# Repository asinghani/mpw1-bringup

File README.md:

# mpw1-bringup

Experiments in salvating SKY130 MPW-ONE chips, 1.5 years after the initial tapeout in December 2020.

### Background

MPW-ONE was the first round of the open-source Google-sponsored tapeout, and as a result of tooling issues with the clock-tree verification, the standard "caravel" padframe used for all chips on the MPW contains timing violations. In this repo I am working with my submission to MPW-ONE and attempting to recover functionality using precise voltage and clock control to reduce the significance of these issues - [asinghani/crypto-accelerator-chip](https://github.com/asinghani/crypto-accelerator-chip)

### Board images

### Progress

- Designed test board (see images above) with a Raspberry Pi Pico and DAC8571
- Implemented firmware (`ctrlfw/remote_ctrl_fw`) and associated Jupyter Notebooks (`notebooks/characterization.ipynb`) for searching possible voltages
- Tested ~50 dies and found some that produced sufficient activity on the Flash memory bus
- Implemented communication protocol in RISC-V assembly which allows bytes to be bit-banged (independent of clock frequency) through the single Caravel GPIO port. This means that non-default GPIO does not need to be enabled in order to get data out of the Caravel core.
- Used this protocol to read the identifier ROMs in the SHA256 and AES cores
- Wrote RISC-V code to Caravel to run short tests of SHA256 and AES256 operations

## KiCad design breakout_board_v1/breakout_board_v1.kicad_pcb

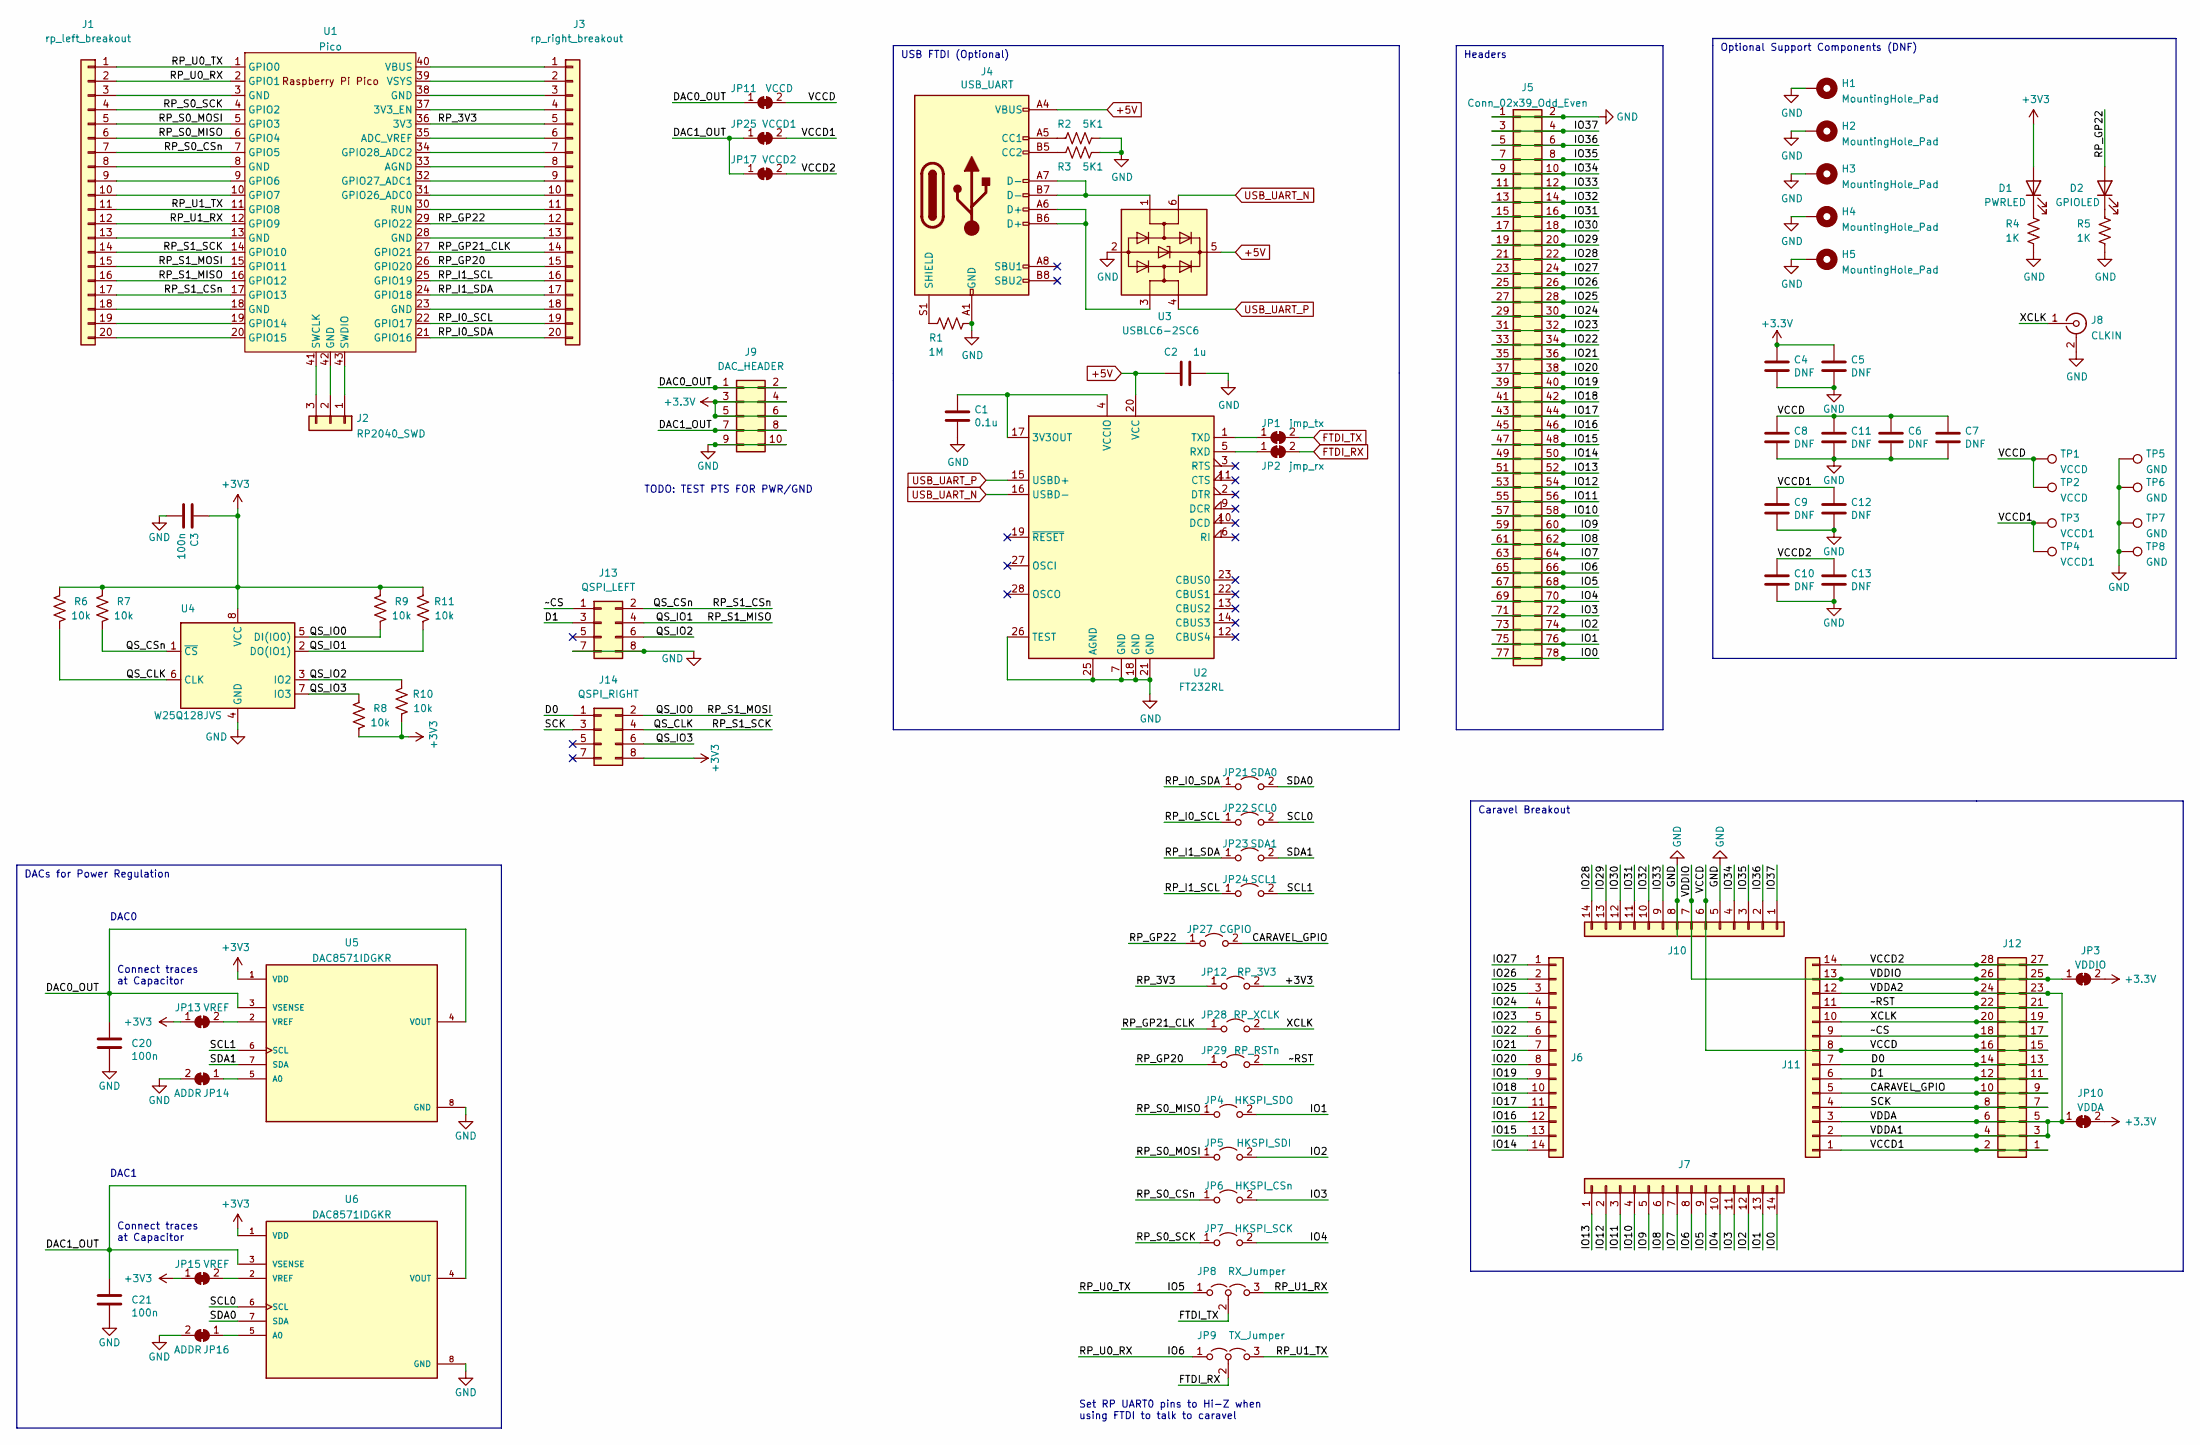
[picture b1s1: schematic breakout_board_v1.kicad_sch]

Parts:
C1: 0.1u; C_0603_1608Metric
C2: 1u; C_0603_1608Metric
C3, C20, C21: 100n; C_0603_1608Metric
C4, C5, C6, C7, C8, C9, C10, C11, C12, C13: DNF; C_0603_1608Metric
D1: PWRLED; LED_0805_2012Metric
D2: GPIOLED; LED_0805_2012Metric
H1, H2, H3, H4, H5: MountingHole_Pad; MountingHole_3.2mm_M3_Pad_Via
J1: rp_left_breakout; PinHeader_1x20_P2.54mm_Vertical
J2: RP2040_SWD; PinHeader_1x03_P2.54mm_Vertical
J3: rp_right_breakout; PinHeader_1x20_P2.54mm_Vertical
J4: USB_UART; USB_C_Receptacle_HRO_TYPE-C-31-M-12
J5: Conn_02x39_Odd_Even; PinHeader_2x39_P2.54mm_Vertical
J6, J7, J10, J11: Conn_01x14; PinHeader_1x14_P1.27mm_Vertical
J8: CLKIN; SMA_Amphenol_132289_EdgeMount
J9: DAC_HEADER; PinHeader_2x05_P2.54mm_Vertical
J12: Conn_02x14_Odd_Even; PinHeader_2x14_P2.54mm_Vertical
J13: QSPI_LEFT; PinHeader_2x04_P2.54mm_Vertical
J14: QSPI_RIGHT; PinHeader_2x04_P2.54mm_Vertical
JP1: jmp_tx; SolderJumper-2_P1.3mm_Bridged_RoundedPad1.0x1.5mm
JP2: jmp_rx; SolderJumper-2_P1.3mm_Bridged_RoundedPad1.0x1.5mm
JP3: VDDIO; SolderJumper-2_P1.3mm_Bridged2Bar_Pad1.0x1.5mm
JP4: HKSPI_SDO; PinHeader_1x02_P2.54mm_Vertical
JP5: HKSPI_SDI; PinHeader_1x02_P2.54mm_Vertical
JP6: HKSPI_CSn; PinHeader_1x02_P2.54mm_Vertical
JP7: HKSPI_SCK; PinHeader_1x02_P2.54mm_Vertical
JP8: RX_Jumper; PinHeader_1x03_P2.54mm_Vertical
JP9: TX_Jumper; PinHeader_1x03_P2.54mm_Vertical
JP10: VDDA; SolderJumper-2_P1.3mm_Bridged2Bar_Pad1.0x1.5mm
JP11: VCCD; SolderJumper-2_P1.3mm_Bridged2Bar_RoundedPad1.0x1.5mm
JP12: RP_3V3; PinHeader_1x02_P2.54mm_Vertical
JP13, JP15: VREF; SolderJumper-2_P1.3mm_Bridged_RoundedPad1.0x1.5mm
JP14, JP16: ADDR; SolderJumper-2_P1.3mm_Bridged_RoundedPad1.0x1.5mm
JP17: VCCD2; SolderJumper-2_P1.3mm_Bridged2Bar_RoundedPad1.0x1.5mm
JP21: SDA0; PinHeader_1x02_P2.54mm_Vertical
JP22: SCL0; PinHeader_1x02_P2.54mm_Vertical
JP23: SDA1; PinHeader_1x02_P2.54mm_Vertical
JP24: SCL1; PinHeader_1x02_P2.54mm_Vertical
JP25: VCCD1; SolderJumper-2_P1.3mm_Bridged2Bar_RoundedPad1.0x1.5mm
JP27: CGPIO; PinHeader_1x02_P2.54mm_Vertical
JP28: RP_XCLK; PinHeader_1x02_P2.54mm_Vertical
JP29: RP_RSTn; PinHeader_1x02_P2.54mm_Vertical
R1: 1M; R_0603_1608Metric
R2, R3: 5K1; R_0603_1608Metric
R4, R5: 1K; R_0603_1608Metric
R6, R7, R8, R9, R10, R11: 10k; R_0603_1608Metric
TP1, TP2: VCCD; TestPoint_Keystone_5000-5004_Miniature
TP3, TP4: VCCD1; TestPoint_Keystone_5000-5004_Miniature
TP5, TP6, TP7, TP8: GND; TestPoint_Keystone_5000-5004_Miniature
U1: Pico; RPi_Pico_SMD_TH
U2: FT232RL; SSOP-28_5.3x10.2mm_P0.65mm
U3: USBLC6-2SC6; SOT-23-6
U4: W25Q128JVS; SOIC-8_5.23x5.23mm_P1.27mm
U5, U6: DAC8571IDGKR; SOP65P490X110-8N; PARTREV July 2003

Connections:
+5V: C2.1, J4.A4 (VBUS), J4.A9 (VBUS), J4.B4 (VBUS), J4.B9 (VBUS), U2.20 (VCC), U3.5 (VBUS)
/CARAVEL_GPIO: J11.5, J12.9, J12.10, JP27.2 (B)
/D0: J11.7, J12.13, J12.14, J14.1
/D1: J11.6, J12.11, J12.12, J13.3
/DAC0_OUT: C20.1, J9.1, J9.2, JP11.1 (A), U5.3 (VSENSE), U5.4 (VOUT)
/DAC1_OUT: C21.1, J9.7, J9.8, JP17.1 (A), JP25.1 (A), U6.3 (VSENSE), U6.4 (VOUT)
/IO0: J5.77, J5.78, J7.14
/IO1: J5.75, J5.76, J7.13, JP4.2 (B)
/IO2: J5.73, J5.74, J7.12, JP5.2 (B)
/IO3: J5.71, J5.72, J7.11, JP6.2 (B)
/IO4: J5.69, J5.70, J7.10, JP7.2 (B)
/IO5: J1.1, J5.67, J5.68, J7.9, JP8.1 (A), U1.1 (GPIO0)
/IO6: J1.2, J5.65, J5.66, J7.8, JP9.1 (A), U1.2 (GPIO1)
/IO7: J5.63, J5.64, J7.7
/IO8: J5.61, J5.62, J7.6
/IO9: J5.59, J5.60, J7.5
/IO10: J5.57, J5.58, J7.4
/IO11: J5.55, J5.56, J7.3
/IO12: J5.53, J5.54, J7.2
/IO13: J5.51, J5.52, J7.1
/IO14: J5.49, J5.50, J6.14
/IO15: J5.47, J5.48, J6.13
/IO16: J5.45, J5.46, J6.12
/IO17: J5.43, J5.44, J6.11
/IO18: J5.41, J5.42, J6.10
/IO19: J5.39, J5.40, J6.9
/IO20: J5.37, J5.38, J6.8
/IO21: J5.35, J5.36, J6.7
/IO22: J5.33, J5.34, J6.6
/IO23: J5.31, J5.32, J6.5
/IO24: J5.29, J5.30, J6.4
/IO25: J5.27, J5.28, J6.3
/IO26: J5.25, J5.26, J6.2
/IO27: J5.23, J5.24, J6.1
/IO28: J5.21, J5.22, J10.14
/IO29: J5.19, J5.20, J10.13
/IO30: J5.17, J5.18, J10.12
/IO31: J5.15, J5.16, J10.11
/IO32: J5.13, J5.14, J10.10
/IO33: J5.11, J5.12, J10.9
/IO34: J5.9, J5.10, J10.4
/IO35: J5.7, J5.8, J10.3
/IO36: J5.5, J5.6, J10.2
/IO37: J5.3, J5.4, J10.1
/QS_CLK: J1.14, J14.4, R6.2, U1.14 (GPIO10), U4.6 (CLK)
/QS_CSn: J1.17, J13.2, R7.2, U1.17 (GPIO13), U4.1 (~CS)
/QS_IO0: J1.15, J14.2, R9.2, U1.15 (GPIO11), U4.5 (DI(IO0))
/QS_IO1: J1.16, J13.4, R11.2, U1.16 (GPIO12), U4.2 (DO(IO1))
/QS_IO2: J13.6, R10.1, U4.3 (IO2)
/QS_IO3: J14.6, R8.1, U4.7 (IO3)
/RP_3V3: J3.5, JP12.1 (A), U1.36 (3V3)
/RP_GP20: J3.15, JP29.1 (A), U1.26 (GPIO20)
/RP_GP21_CLK: J3.14, JP28.1 (A), U1.27 (GPIO21)
/RP_GP22: D2.2 (A), J3.12, JP27.1 (A), U1.29 (GPIO22)
/RP_I0_SCL: J3.19, JP22.1 (A), U1.22 (GPIO17)
/RP_I0_SDA: J3.20, JP21.1 (A), U1.21 (GPIO16)
/RP_I1_SCL: J3.16, JP24.1 (A), U1.25 (GPIO19)
/RP_I1_SDA: J3.17, JP23.1 (A), U1.24 (GPIO18)
/RP_S0_CSn: J1.7, JP6.1 (A), U1.7 (GPIO5)
/RP_S0_MISO: J1.6, JP4.1 (A), U1.6 (GPIO4)
/RP_S0_MOSI: J1.5, JP5.1 (A), U1.5 (GPIO3)
/RP_S0_SCK: J1.4, JP7.1 (A), U1.4 (GPIO2)
/RP_U1_RX: J1.12, JP8.3 (B), U1.12 (GPIO9)
/RP_U1_TX: J1.11, JP9.3 (B), U1.11 (GPIO8)
/SCK: J11.4, J12.7, J12.8, J14.3
/SCL0: JP22.2 (B), U6.6 (SCL)
/SCL1: JP24.2 (B), U5.6 (SCL)
/SDA0: JP21.2 (B), U6.7 (SDA)
/SDA1: JP23.2 (B), U5.7 (SDA)
/VCCD: C6.1, C7.1, C8.1, C11.1, J10.6, J11.8, J12.15, J12.16, JP11.2 (B), TP1.1, TP2.1
/VCCD1: C9.1, C12.1, J11.1, J12.1, J12.2, JP25.2 (B), TP3.1, TP4.1
/VCCD2: C10.1, C13.1, J11.14, J12.27, J12.28, JP17.2 (B)
/VDDA: J11.2, J11.3, J11.12, J12.3, J12.4, J12.5, J12.6, J12.23, J12.24, JP10.1 (A)
/VDDIO: J10.7, J11.13, J12.25, J12.26, JP3.1 (A)
/XCLK: J8.1 (In), J11.10, J12.19, J12.20, JP28.2 (B)
/~CS: J11.9, J12.17, J12.18, J13.1
/~RST: J11.11, J12.21, J12.22, JP29.2 (B)
FTDI_RX: JP2.2 (B), JP9.2 (C)
FTDI_TX: JP1.2 (B), JP8.2 (C)
GND: C1.2, C2.2, C3.2, C4.2, C5.2, C6.2, C7.2, C8.2, C9.2, C10.2, C11.2, C12.2, C13.2, C20.2, C21.2, H1.1, H2.1, H3.1, H4.1, H5.1, J4.A1 (GND), J4.A12 (GND), J4.B1 (GND), J4.B12 (GND), J5.1, J5.2, J8.2 (Ext), J9.9, J9.10, J10.5, J10.8, J13.7, J13.8, JP14.2 (B), JP16.2 (B), R1.2, R2.2, R3.2, R4.2, R5.2, TP5.1, TP6.1, TP7.1, TP8.1, U2.7 (GND), U2.18 (GND), U2.21 (GND), U2.25 (AGND), U2.26 (TEST), U3.2 (GND), U4.4 (GND), U5.8 (GND), U6.8 (GND)
unnamed: C1.1, U2.4 (VCCIO), U2.17 (3V3OUT)
unnamed: D1.1 (K), R4.1
unnamed: D2.1 (K), R5.1
unnamed: J1.3, U1.3 (GND)
unnamed: J1.8, U1.8 (GND)
unnamed: J1.9, U1.9 (GPIO6)
unnamed: J1.10, U1.10 (GPIO7)
unnamed: J1.13, U1.13 (GND)
unnamed: J1.18, U1.18 (GND)
unnamed: J1.19, U1.19 (GPIO14)
unnamed: J1.20, U1.20 (GPIO15)
unnamed: J2.1, U1.43 (SWDIO)
unnamed: J2.2, U1.42 (GND)
unnamed: J2.3, U1.41 (SWCLK)
unnamed: J3.1, U1.40 (VBUS)
unnamed: J3.2, U1.39 (VSYS)
unnamed: J3.3, U1.38 (GND)
unnamed: J3.4, U1.37 (3V3_EN)
unnamed: J3.6, U1.35 (ADC_VREF)
unnamed: J3.7, U1.34 (GPIO28_ADC2)
unnamed: J3.8, U1.33 (AGND)
unnamed: J3.9, U1.32 (GPIO27_ADC1)
unnamed: J3.10, U1.31 (GPIO26_ADC0)
unnamed: J3.11, U1.30 (RUN)
unnamed: J3.13, U1.28 (GND)
unnamed: J3.18, U1.23 (GND)
unnamed: J4.A5 (CC1), R2.1
unnamed: J4.A6 (D+), J4.B6 (D+), U3.3 (I/O2)
unnamed: J4.A7 (D-), J4.B7 (D-), U3.1 (I/O1)
unnamed: J4.B5 (CC2), R3.1
unnamed: J4.S1 (SHIELD), R1.1
unnamed: JP1.1 (A), U2.1 (TXD)
unnamed: JP2.1 (A), U2.5 (RXD)
unnamed: JP13.2 (B), U5.2 (VREF)
unnamed: JP14.1 (A), U5.5 (A0)
unnamed: JP15.2 (B), U6.2 (VREF)
unnamed: JP16.1 (A), U6.5 (A0)
USB_UART_N: U2.16 (USBD-), U3.6 (I/O1)
USB_UART_P: U2.15 (USBD+), U3.4 (I/O2)

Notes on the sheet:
Set RP UART0 pins to Hi-Z when using FTDI to talk to caravel
DAC0
DACs for Power Regulation
USB FTDI (Optional)
Optional Support Components (DNF)
Caravel Breakout
TODO: TEST PTS FOR PWR/GND
DAC1
Connect traces at Capacitor
Headers

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
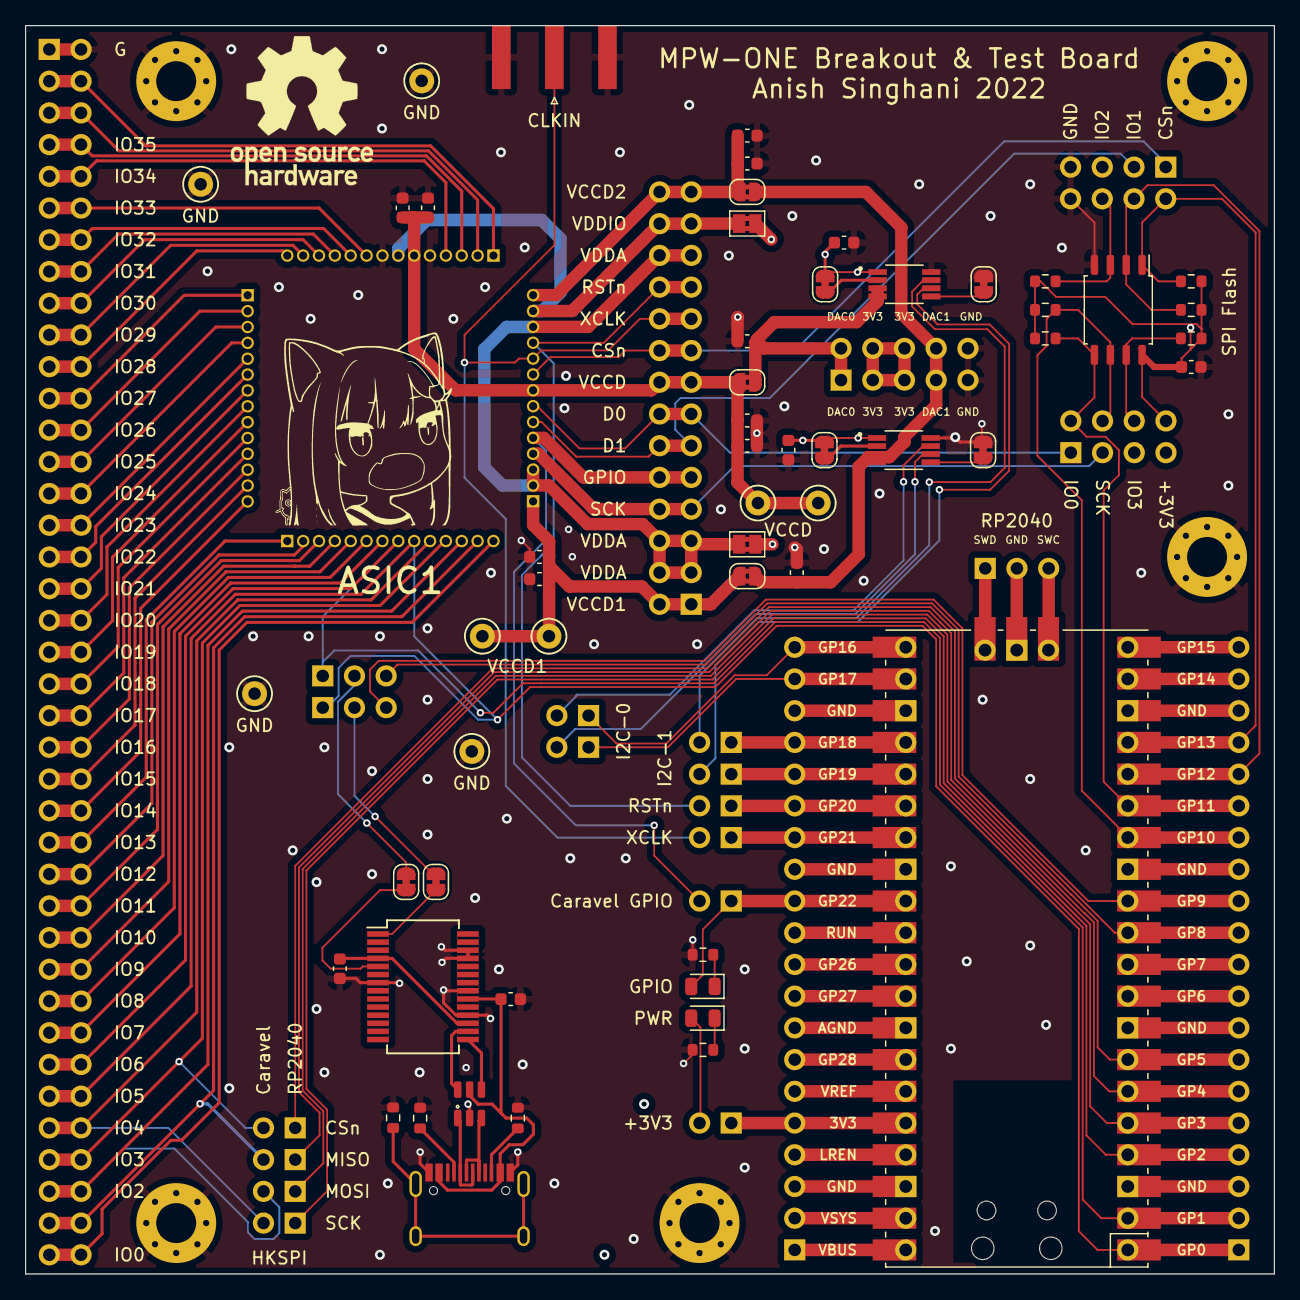
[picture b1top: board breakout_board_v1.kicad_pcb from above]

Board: 4 copper layers, 100.0 x 100.0 mm, 86 parts (0 on the bottom side), 120 nets.

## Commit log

2022-01-30 Add initial version of breakout board
2022-02-28 Add datasheets
2022-03-01 IT WORKS
2022-03-03 remote-control code and notebooks for running tests remotely from a host machine
